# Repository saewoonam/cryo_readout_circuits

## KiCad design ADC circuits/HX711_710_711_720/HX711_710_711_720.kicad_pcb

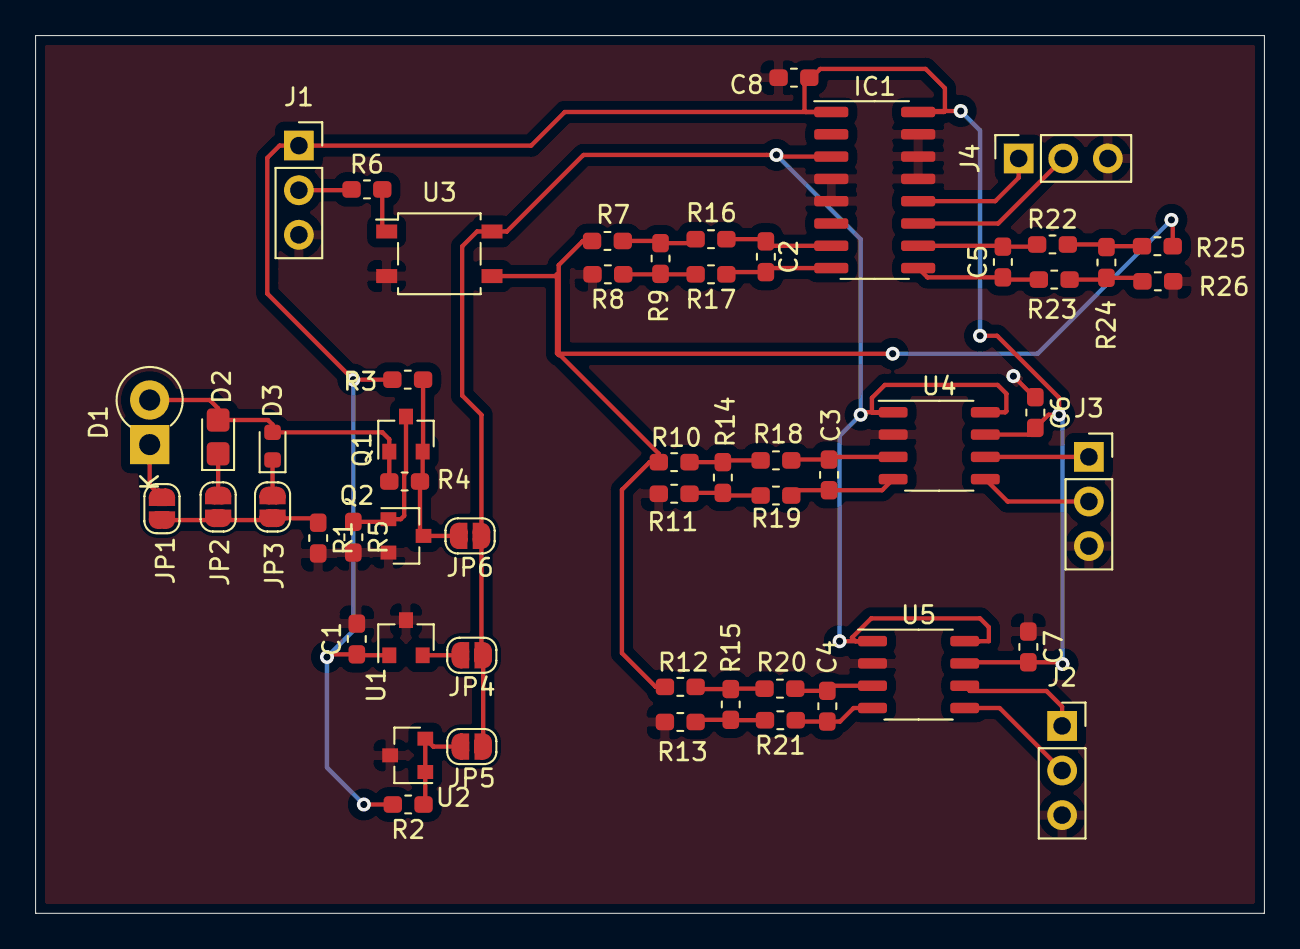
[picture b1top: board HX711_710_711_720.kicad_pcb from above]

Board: 2 copper layers, 70.0 x 50.0 mm, 55 parts (0 on the bottom side), 37 nets.

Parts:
C1: 470nF; C_0603_1608Metric_Pad1.05x0.95mm_HandSolder
C2, C3, C4, C5, C6, C7, C8: 100nF; C_0603_1608Metric_Pad1.05x0.95mm_HandSolder
D1: LTL-4231; D_DO-15_P2.54mm_Vertical_KathodeUp
D2: C2297; D_0805_2012Metric_Castellated
D3: 19-217/GHC-YR1S2/3T; D_0603_1608Metric
IC1: HX711; SOIC-16_3.9x9.9mm_P1.27mm
J1, J2, J3, J4: Conn_01x03_Female; PinSocket_1x03_P2.54mm_Vertical
JP1, JP2, JP3, JP4, JP5, JP6: NO; SolderJumper-2_P1.3mm_Open_RoundedPad1.0x1.5mm
Q1: MMBT3906; SOT-23
Q2: MMBT2222A; SOT-23
R1: 75; R_0603_1608Metric_Pad1.05x0.95mm_HandSolder
R2, R3: 300; R_0603_1608Metric_Pad1.05x0.95mm_HandSolder
R4, R5, R6, R9, R14, R15, R24: 1K; R_0603_1608Metric_Pad1.05x0.95mm_HandSolder
R7, R8, R10, R11, R12, R13, R25, R26: 10Meg; R_0603_1608Metric_Pad1.05x0.95mm_HandSolder
R16, R17, R18, R19, R20, R21, R22, R23: 100; R_0603_1608Metric_Pad1.05x0.95mm_HandSolder
U1: REF3020; SOT-23
U2: TL431DBZ; SOT-23
U3: AQW282SX; SO-4_4.4x4.3mm_P2.54mm
U4: HX710B; SOP-8_3.9x4.9mm_P1.27mm
U5: HX710C; SOP-8_3.9x4.9mm_P1.27mm

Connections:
+3V3: C1.1, C6.2, C7.2, C8.1, IC1.1, IC1.16, J1.1, R2.2, R3.2, U1.1, U4.7, U5.7
/sig: R7.2, R10.2, R12.2, R25.2, U3.3
/vref: IC1.3, JP4.1, JP5.1, JP6.1, U3.4, U4.1, U4.8, U5.1, U5.8
GND: C1.2, C6.1, C7.1, C8.2, IC1.4, IC1.5, IC1.13, IC1.14, IC1.15, J1.3, J2.3, J3.3, J4.3, Q2.2, R1.2, R5.2, R8.2, R11.2, R13.2, R26.2, U1.3, U2.3, U3.2, U4.2, U5.2
unnamed: C2.1, IC1.8, R17.1
unnamed: C2.2, IC1.7, R16.1
unnamed: C3.1, R19.1, U4.4
unnamed: C3.2, R18.1, U4.3
unnamed: C4.1, R21.1, U5.4
unnamed: C4.2, R20.1, U5.3
unnamed: C5.1, IC1.9, R23.1
unnamed: C5.2, IC1.10, R22.1
unnamed: D1.1, JP1.1
unnamed: D1.2, D2.2, D3.2, Q1.1, R4.2
unnamed: D2.1, JP2.1
unnamed: D3.1, JP3.1
unnamed: IC1.11, J4.2
unnamed: IC1.12, J4.1
unnamed: J1.2, R6.1
unnamed: J2.1, U5.6
unnamed: J2.2, U5.5
unnamed: J3.1, U4.6
unnamed: J3.2, U4.5
unnamed: JP1.2, JP2.2, JP3.2, R1.1
unnamed: JP4.2, U1.2
unnamed: JP5.2, R2.1, U2.1, U2.2
unnamed: JP6.2, Q1.2, Q2.3, R3.1, R4.1
unnamed: Q1.3, Q2.1, R5.1
unnamed: R6.2, U3.1
unnamed: R10.1, R14.1, R18.2
unnamed: R11.1, R14.2, R19.2
unnamed: R12.1, R15.1, R20.2
unnamed: R13.1, R15.2, R21.2
unnamed: R7.1, R9.1, R16.2
unnamed: R8.1, R9.2, R17.2
unnamed: R22.2, R24.1, R25.1
unnamed: R23.2, R24.2, R26.1

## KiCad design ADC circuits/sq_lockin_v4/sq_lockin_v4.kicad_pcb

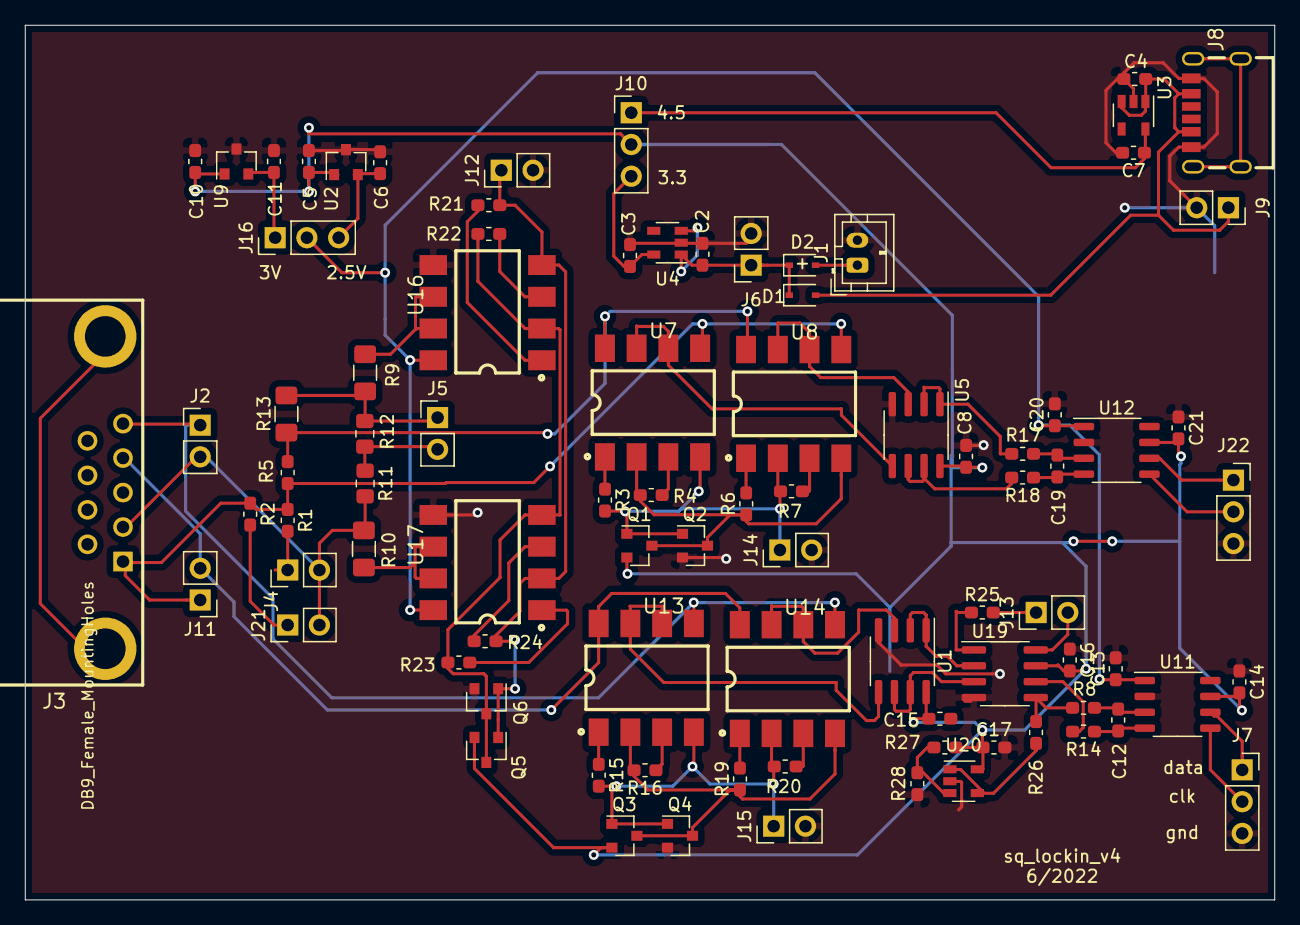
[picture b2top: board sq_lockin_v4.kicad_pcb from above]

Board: 2 copper layers, 100.0 x 70.0 mm, 88 parts (0 on the bottom side), 62 nets.

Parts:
C2, C3, C4, C5, C6, C7, C10, C11: 1uF; C_0603_1608Metric_Pad1.05x0.95mm_HandSolder
C8, C12, C13, C14, C15, C16, C17, C19, C20, C21: 100nF; C_0603_1608Metric_Pad1.05x0.95mm_HandSolder
D1, D2: LBAT54HT1G; D_SOD-323
J1: battery; JST_PH_B2B-PH-K_1x02_P2.00mm_Vertical
J2, J4, J5, J11, J12, J13, J14, J15, J21: Conn_01x02_Male_2.54mm; PinHeader_1x02_P2.54mm_Vertical
J3: DB9_Female_MountingHoles; DSUB-TH_DS1037-09FNAKT74-0CC
J6, J9: receptacle; PinSocket_1x02_P2.54mm_Vertical
J7, J22: Conn_01x03_Female; PinSocket_1x03_P2.54mm_Vertical
J8: USB_C_KoreanHroparts_6P; USB-C-KoreanHroparts
J10, J16: Conn_01x03_Male; PinHeader_1x03_P2.54mm_Vertical
Q1, Q3, Q5: BSS84; SOT-23
Q2, Q4, Q6: 2N7002; SOT-23
R1: 10K 0.1%; R_0603_1608Metric_Pad1.05x0.95mm_HandSolder
R2: 1K 0.1%; R_0603_1608Metric_Pad1.05x0.95mm_HandSolder
R3, R4, R6, R7, R15, R16, R19, R20, R21, R22, R23, R24: 200; R_0603_1608Metric_Pad1.05x0.95mm_HandSolder
R5: 100K_0.1%; R_0603_1608Metric_Pad1.05x0.95mm_HandSolder
R8, R14, R17, R18, R25: 100; R_0603_1608Metric_Pad1.05x0.95mm_HandSolder
R9, R10, R13: 1M_0.1%; R_1206_3216Metric_Pad1.42x1.75mm_HandSolder
R11: 5K_0.1%; R_0805_2012Metric_Pad1.15x1.40mm_HandSolder
R12: 75K_0.1%; R_0805_2012Metric_Pad1.15x1.40mm_HandSolder
R26: 10; R_0603_1608Metric_Pad1.05x0.95mm_HandSolder
R27, R28: 10K; R_0603_1608Metric_Pad1.05x0.95mm_HandSolder
U1, U5: OPA2376xxDGK; SOIC-8_3.9x4.9mm_P1.27mm
U2: REF3325; SOT-23
U3: LP5907MFX-4.5; SOT-23-5
U4: LP5907MFX-3.3; SOT-23-5
U7, U8, U13, U14, U16, U17: AQW212EHAX; SMD-8_L9.8-W6.4-P2.54-LS10.0-BL
U9: REF3030; SOT-23
U11, U12: HX710C; SOP-8_3.9x4.9mm_P1.27mm
U19: AD623; SOIC-8_3.9x4.9mm_P1.27mm
U20: OPA333xxDBV; SOT-23-5

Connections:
+3V3: C3.1, J10.3, U4.5
+4V: C7.1, J10.1, U3.5
/I+: J3.1, J11.1, R1.1, R2.1, R5.1, U7.5, U8.5
/I-: J2.2, J3.2, J4.2, J21.2, R10.2, R11.2
/Sheet621A3D16/in+: U5.5, U7.6, U7.7
/Sheet621A3D16/in-: U5.3, U8.6, U8.7
/Sheet624B5D4E/ctrl+: J14.1, Q1.1, Q2.1, R3.2, R7.1, U7.4, U8.2
/Sheet624B5D4E/ctrl-: Q1.3, Q2.3, R4.2, R6.1, U7.2, U8.4
/Sheet624B5D4E/in+: R5.2, R13.1, U7.8, U8.8
/Sheet6275CBF8/in+: U1.5, U13.6, U13.7
/Sheet6275CBF8/in-: U1.3, U14.6, U14.7
/Sheet62237673/V+: R18.2, U5.6, U5.7
/Sheet62237673/V-: R17.2, U5.1, U5.2
/V+: J3.4, J11.2, U13.8, U14.8
/V-: J2.1, J3.5, U13.5, U14.5
/sheet624D2E57/V+: R14.2, U19.6
/sheet624D2E57/V-: R8.2, R26.2, U19.5
/sheet624D2E58/ctrl+: J15.1, Q3.1, Q4.1, R15.2, R20.1, U13.4, U14.2
/sheet624D2E58/ctrl-: Q3.3, Q4.3, R16.2, R19.1, U13.2, U14.4
/sheet6256EE2A/ctrl+: J12.1, Q5.1, Q6.1, R21.2, R24.1, U16.4, U17.2
/sheet6256EE2A/ctrl-: Q5.3, Q6.3, R22.2, R23.1, U16.2, U17.4
/sheet6256EE2A/out+: R9.2, U16.6, U16.7
/sheet6256EE2A/out-: R10.1, U17.6, U17.7
/vref: C13.1, C20.1, J16.2, U11.1, U12.1, U16.8, U17.8
/vref1: C6.1, J16.3, U2.2
/vref2: C11.1, J16.1, U9.2
GND: C2.2, C3.2, C4.2, C5.2, C6.2, C7.2, C8.2, C10.2, C11.2, C13.2, C14.1, C16.1, C17.2, C20.2, C21.1, J1.2, J6.2, J7.3, J8.A12, J8.B12, J9.2, J12.2, J14.2, J15.2, J22.3, Q2.2, Q4.2, Q6.2, R28.2, U1.4, U2.3, U3.2, U4.2, U5.4, U9.3, U11.2, U12.2, U16.5, U17.5, U19.4, U20.2
unnamed: C2.1, D1.1, D2.1, J6.1, U4.1, U4.3
unnamed: C4.1, D1.2, J8.A9, J8.B9, J9.1, U3.1, U3.3
unnamed: C12.1, R14.1, U11.4
unnamed: C12.2, R8.1, U11.3
unnamed: C19.1, R18.1, U12.4
unnamed: C19.2, R17.1, U12.3
unnamed: D2.2, J1.1
unnamed: J4.1, R1.2
unnamed: J5.1, R9.1, R12.1, R13.2
unnamed: J5.2, R11.1, R12.2
unnamed: J7.1, U11.6
unnamed: J7.2, U11.5
unnamed: J13.1, R25.2
unnamed: J13.2, U19.8
unnamed: J21.1, R2.2
unnamed: J22.1, U12.6
unnamed: J22.2, U12.5
unnamed: R3.1, U7.1
unnamed: R4.1, U7.3
unnamed: R6.2, U8.1
unnamed: R7.2, U8.3
unnamed: R15.1, U13.1
unnamed: R16.1, U13.3
unnamed: R19.2, U14.1
unnamed: R20.2, U14.3
unnamed: R21.1, U16.1
unnamed: R22.1, U16.3
unnamed: R23.2, U17.1
unnamed: R24.2, U17.3
unnamed: R25.1, U19.1
unnamed: R26.1, U20.1, U20.4
unnamed: R27.2, R28.1, U20.3
unnamed: U1.1, U1.2, U19.2
unnamed: U1.6, U1.7, U19.3
VCC: C5.1, C8.1, C10.1, C14.2, C15.1, C16.2, C17.1, C21.2, J10.2, Q1.2, Q3.2, Q5.2, R27.1, U1.8, U2.1, U5.8, U9.1, U11.7, U12.7, U19.7, U20.5

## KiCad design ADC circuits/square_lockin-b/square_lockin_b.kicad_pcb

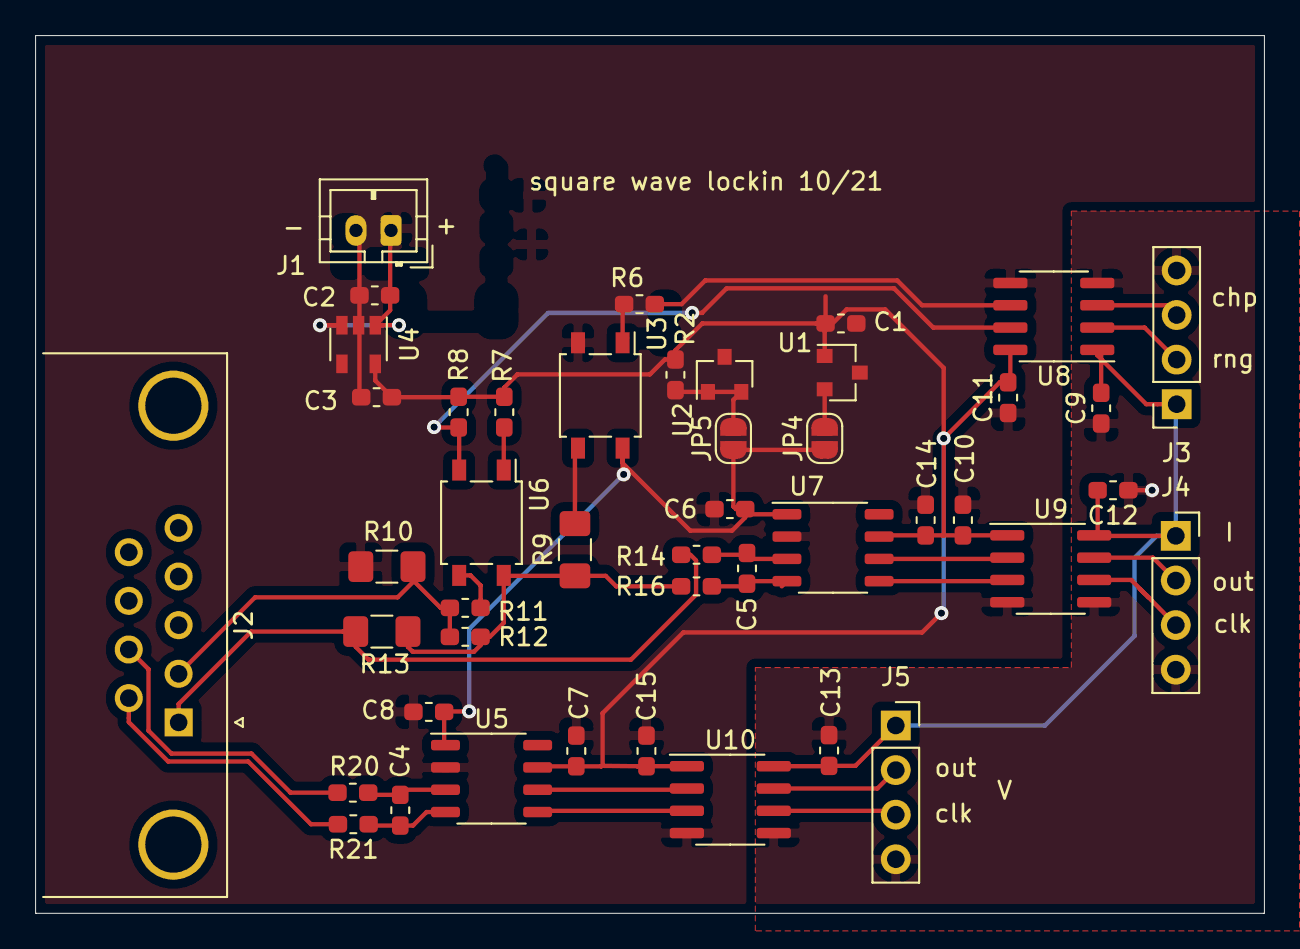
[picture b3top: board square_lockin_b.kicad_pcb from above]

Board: 2 copper layers, 70.0 x 50.0 mm, 45 parts (0 on the bottom side), 33 nets.

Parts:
C1: 470nF; C_0603_1608Metric_Pad1.05x0.95mm_HandSolder
C2, C3: 1uF; C_0603_1608Metric_Pad1.05x0.95mm_HandSolder
C4, C5, C6, C7, C8, C9, C10, C11, C12, C13, C14, C15: 100nF; C_0603_1608Metric_Pad1.05x0.95mm_HandSolder
J1: JST-B2B-PH; JST_PH_B2B-PH-K_1x02_P2.00mm_Vertical
J2: DB9_Female; DSUB-9_Female_Horizontal_P2.77x2.84mm_EdgePinOffset4.94mm_H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
J3, J4, J5: Conn_01x04_Female; PinSocket_1x04_P2.54mm_Vertical
JP4, JP5: NO; SolderJumper-2_P1.3mm_Open_RoundedPad1.0x1.5mm
R2: 300; R_0603_1608Metric_Pad1.05x0.95mm_HandSolder
R6, R7, R8: 1K; R_0603_1608Metric_Pad1.05x0.95mm_HandSolder
R9, R10, R13: 1M_0.1%; R_1206_3216Metric_Pad1.42x1.75mm_HandSolder
R11: 2.2K_0.1%; R_0603_1608Metric_Pad1.05x0.95mm_HandSolder
R12: 22K_0.1%; R_0603_1608Metric_Pad1.05x0.95mm_HandSolder
R14, R16, R20, R21: 100; R_0603_1608Metric_Pad1.05x0.95mm_HandSolder
U1: REF3020; SOT-23
U2: TL431DBZ; SOT-23
U3, U6: AQW282SX; SO-4_4.4x4.3mm_P2.54mm
U4: LP5907MFX-3.3; SOT-23-5
U5, U7: HX710C; SOP-8_3.9x4.9mm_P1.27mm
U8: PI120; SOIC-8_3.9x4.9mm_P1.27mm
U9, U10: PI121; SOIC-8_3.9x4.9mm_P1.27mm

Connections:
+3.3VP: C9.2, C12.2, C13.2, J3.1, J4.1, J5.1, U8.1, U9.8, U10.8
+3V3: C1.1, C3.1, C7.2, C10.2, C11.2, C14.2, C15.2, R2.2, R7.2, R8.2, U1.1, U4.5, U5.7, U7.7, U8.8, U9.1, U10.1
/I+: J2.1, R13.1, R14.2
/I-: J2.2, R10.1, R11.2, R12.2
/V+: J2.6, R21.2
/V-: J2.7, R20.2
/range_toggle: R8.1, U6.2, U8.7
/sig: R9.2, U3.3
/vref: C6.1, C8.1, JP4.1, JP5.1, U3.4, U5.1, U7.1
GND: C1.2, C2.2, C3.2, C6.2, C7.1, C8.2, C10.1, C11.1, C14.1, C15.1, J1.2, R10.2, U1.3, U2.3, U3.2, U4.2, U5.2, U7.2, U8.5, U9.4, U10.4
GNDD: C9.1, C12.1, C13.1, J3.4, J4.4, J5.4, U8.4, U9.5, U10.5
unnamed: C2.1, J1.1, U4.1, U4.3
unnamed: C4.1, R21.1, U5.4
unnamed: C4.2, R20.1, U5.3
unnamed: C5.1, R16.1, U7.4
unnamed: C5.2, R14.1, U7.3
unnamed: J3.2, U8.2
unnamed: J3.3, U8.3
unnamed: J4.2, U9.7
unnamed: J4.3, U9.6
unnamed: J5.2, U10.7
unnamed: J5.3, U10.6
unnamed: JP4.2, U1.2
unnamed: JP5.2, R2.1, U2.1, U2.2
unnamed: R6.1, U8.6
unnamed: R6.2, U3.1
unnamed: R7.1, U6.1
unnamed: R11.1, U6.3
unnamed: R9.1, R12.1, R13.2, R16.2, U6.4
unnamed: U7.5, U9.3
unnamed: U7.6, U9.2
unnamed: U5.6, U10.2
unnamed: U5.5, U10.3

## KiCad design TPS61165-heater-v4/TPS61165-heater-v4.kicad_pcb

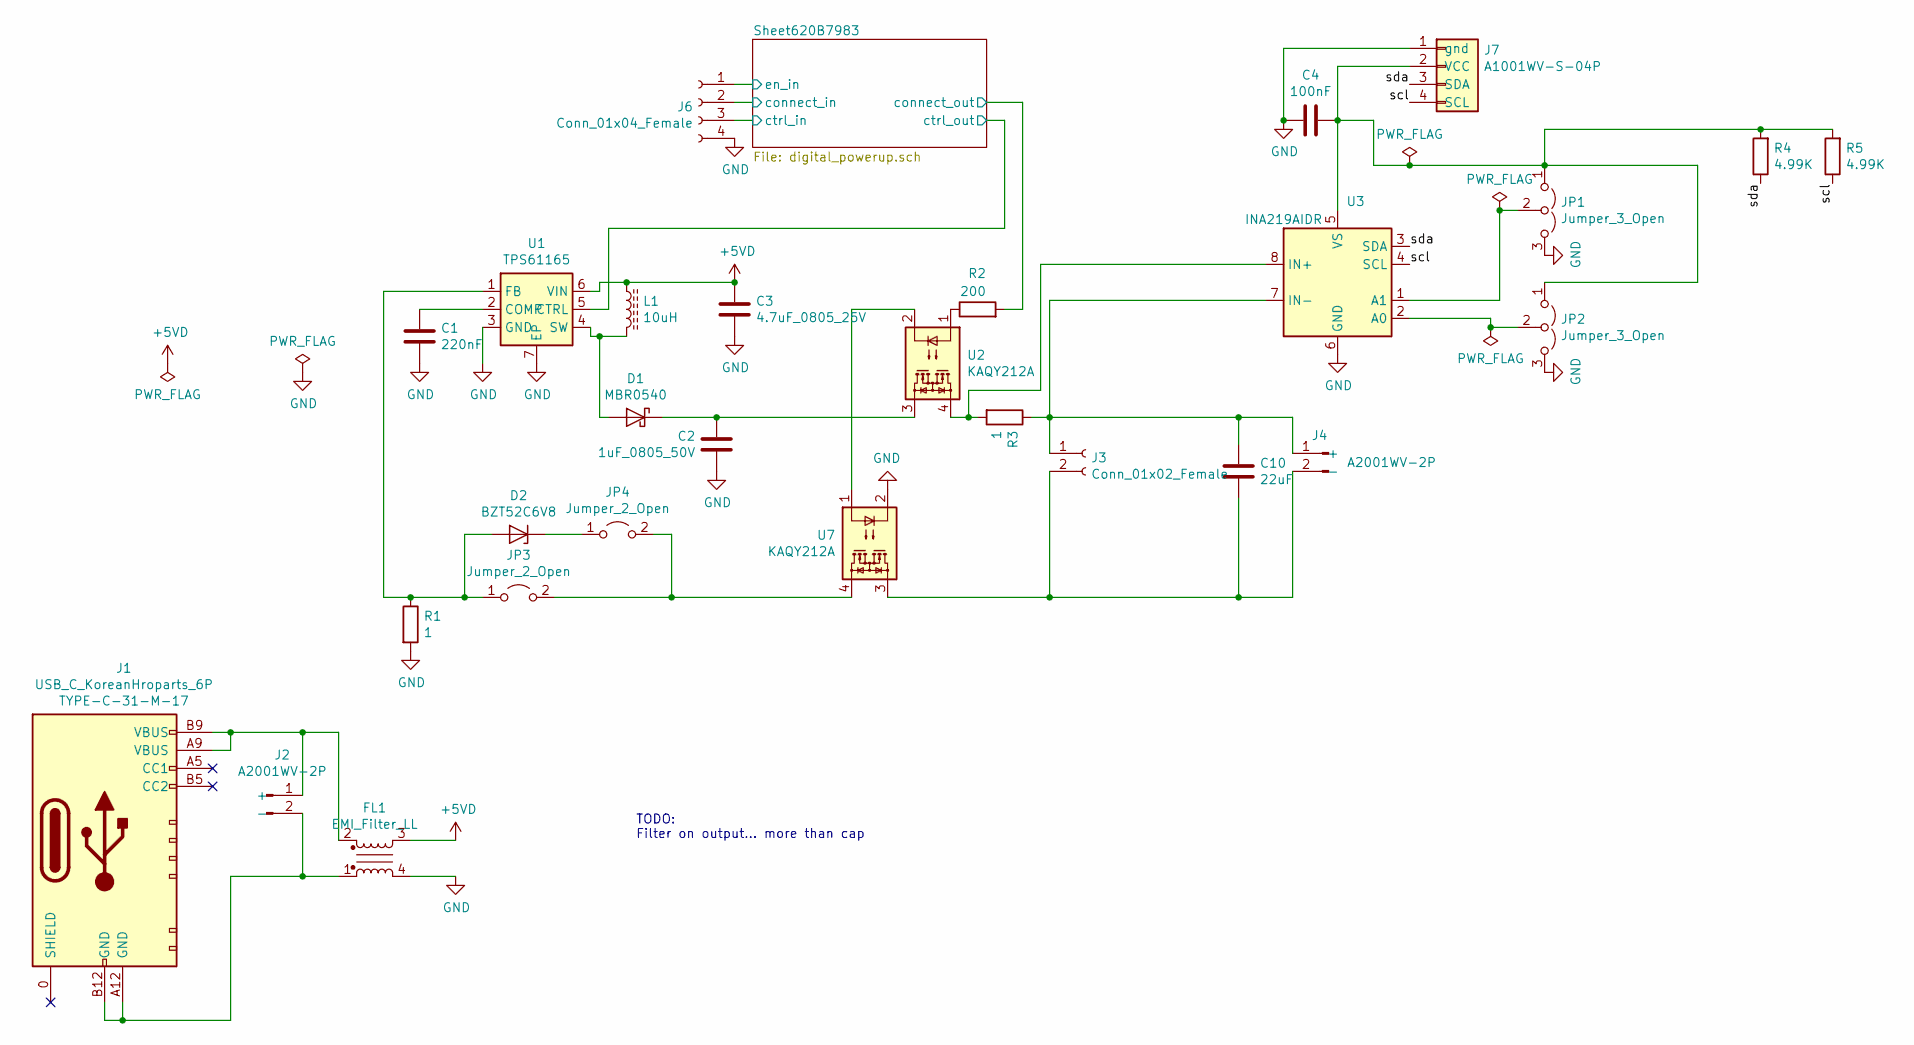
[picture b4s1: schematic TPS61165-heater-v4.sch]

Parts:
C1: 220nF; C_0603_1608Metric_Pad1.05x0.95mm_HandSolder; MPN CL10B224KA8NNNC; LCSC C21120
C2: 1uF_0805_50V; C_0805_2012Metric_Pad1.15x1.40mm_HandSolder; MPN CL21B105KBFNNNE; LCSC C28323
C3: 4.7uF_0805_25V; C_0805_2012Metric_Pad1.15x1.40mm_HandSolder; MPN CC0805KKX7R8BB475; LCSC C354262
C4: 100nF; C_0603_1608Metric_Pad1.05x0.95mm_HandSolder; MPN CC0603KRX7R9BB104; LCSC C14663
C10: 22uF; C_2220_5650Metric_Pad1.97x5.40mm_HandSolder; MPN FS55X226K500EHG; LCSC C784103
D1: MBR0540; D_SOD-123; MPN MBR0540T1G; LCSC C21353
D2: BZT52C6V8; D_SOD-123; MPN BZT52C6V8; LCSC C173404
FL1: EMI_Filter_LL; FILTER-SMD_4P-L4.5-W3.2-BL_CMF4532L_1812; MPN ACT45L-201-2P-TL000; LCSC C131445
J1: USB_C_KoreanHroparts_6P; USB-C-KoreanHroparts; MPN TYPE-C-31-M-17; LCSC C283540
J2, J4: A2001WV-2P; JST_PH_B2B-PH-K_1x02_P2.00mm_Vertical; MPN A2001WV-2P; LCSC C225188
J3: Conn_01x02_Female; PinSocket_1x02_P2.54mm_Vertical; LCSC C49661
J6: Conn_01x04_Female; PinSocket_1x04_P2.54mm_Vertical; MPN B-2200S04P-A120; LCSC C124413
J7: A1001WV-S-04P; JST_SH_BM04B-SRSS-TB_1x04-1MP_P1.00mm_Vertical; MPN A1001WV-S-04P; LCSC C371588
JP1, JP2: Jumper_3_Open; SolderJumper-3_P1.3mm_Open_Pad1.0x1.5mm
JP3, JP4: Jumper_2_Open; SolderJumper-2_P1.3mm_Open_RoundedPad1.0x1.5mm
L1: 10uH; IND-SMD_L4.7-W4.7; MPN VLCF5020T-100M1R1-1; LCSC C212280
R1, R3: 1; R_0603_1608Metric_Pad1.05x0.95mm_HandSolder; MPN 0603WAF100KT5E; LCSC C22936
R2: 200; R_0603_1608Metric_Pad1.05x0.95mm_HandSolder; MPN 0603WAF2000T5E; LCSC C8218
R4, R5: 4.99K; R_0603_1608Metric_Pad1.05x0.95mm_HandSolder; MPN 0603WAF4991T5E; LCSC C23046
U1: TPS61165; WSON-6-1EP_2x2mm_P0.65mm_EP1x1.6mm; MPN TPS61165DRVR; LCSC C122568
U2, U7: KAQY212A; SMD-4_L4.6-W6.4-P2.54-LS10.0-BR; MPN KAQY212A; LCSC C194713
U3: INA219AIDR; SOIC-8_3.9x4.9mm_P1.27mm; MPN INA219AIDR; LCSC C138706

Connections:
+5VD: C3.1, FL1.3, L1.1, U1.6 (VIN); also elsewhere on the board
/Sheet620B7983/connect_in: J6.2; also elsewhere on the board
/Sheet620B7983/connect_out: R2.2; also elsewhere on the board
/Sheet620B7983/ctrl_in: J6.3; also elsewhere on the board
/Sheet620B7983/ctrl_out: U1.5 (CTRL); also elsewhere on the board
/Sheet620B7983/en_in: J6.1; also elsewhere on the board
/scl: J7.4 (SCL), R5.1, U3.4 (SCL)
/sda: J7.3 (SDA), R4.1, U3.3 (SDA)
GND: C1.2, C2.2, C3.2, C4.2, FL1.4, J6.4, J7.1 (gnd), JP1.3 (B), JP2.3 (B), R1.2, U1.3 (GND), U1.7 (EP), U3.6 (GND), U7.2; also elsewhere on the board
unnamed: C1.1, U1.2 (COMP)
unnamed: C2.1, D1.1 (K), U2.3
unnamed: C4.1, J7.2 (VCC), JP1.1 (A), JP2.1 (A), R4.2, R5.2, U3.5 (VS)
unnamed: C10.1, J3.1, J4.1 (+), R3.1, U3.7 (IN-)
unnamed: C10.2, J3.2, J4.2 (-), U7.3
unnamed: D1.2 (A), L1.2, U1.4 (SW)
unnamed: D2.1 (K), JP4.1 (A)
unnamed: D2.2 (A), JP3.1 (A), R1.1, U1.1 (FB)
unnamed: FL1.1, J1.A12 (GND), J1.B12 (GND), J2.2 (-)
unnamed: FL1.2, J1.A9 (VBUS), J1.B9 (VBUS), J2.1 (+)
unnamed: JP1.2 (C), U3.1 (A1)
unnamed: JP2.2 (C), U3.2 (A0)
unnamed: JP3.2 (B), JP4.2 (B), U7.4
unnamed: R2.1, U2.1
unnamed: R3.2, U2.4, U3.8 (IN+)
unnamed: U2.2, U7.1

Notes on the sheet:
TODO: Filter on output… more than cap

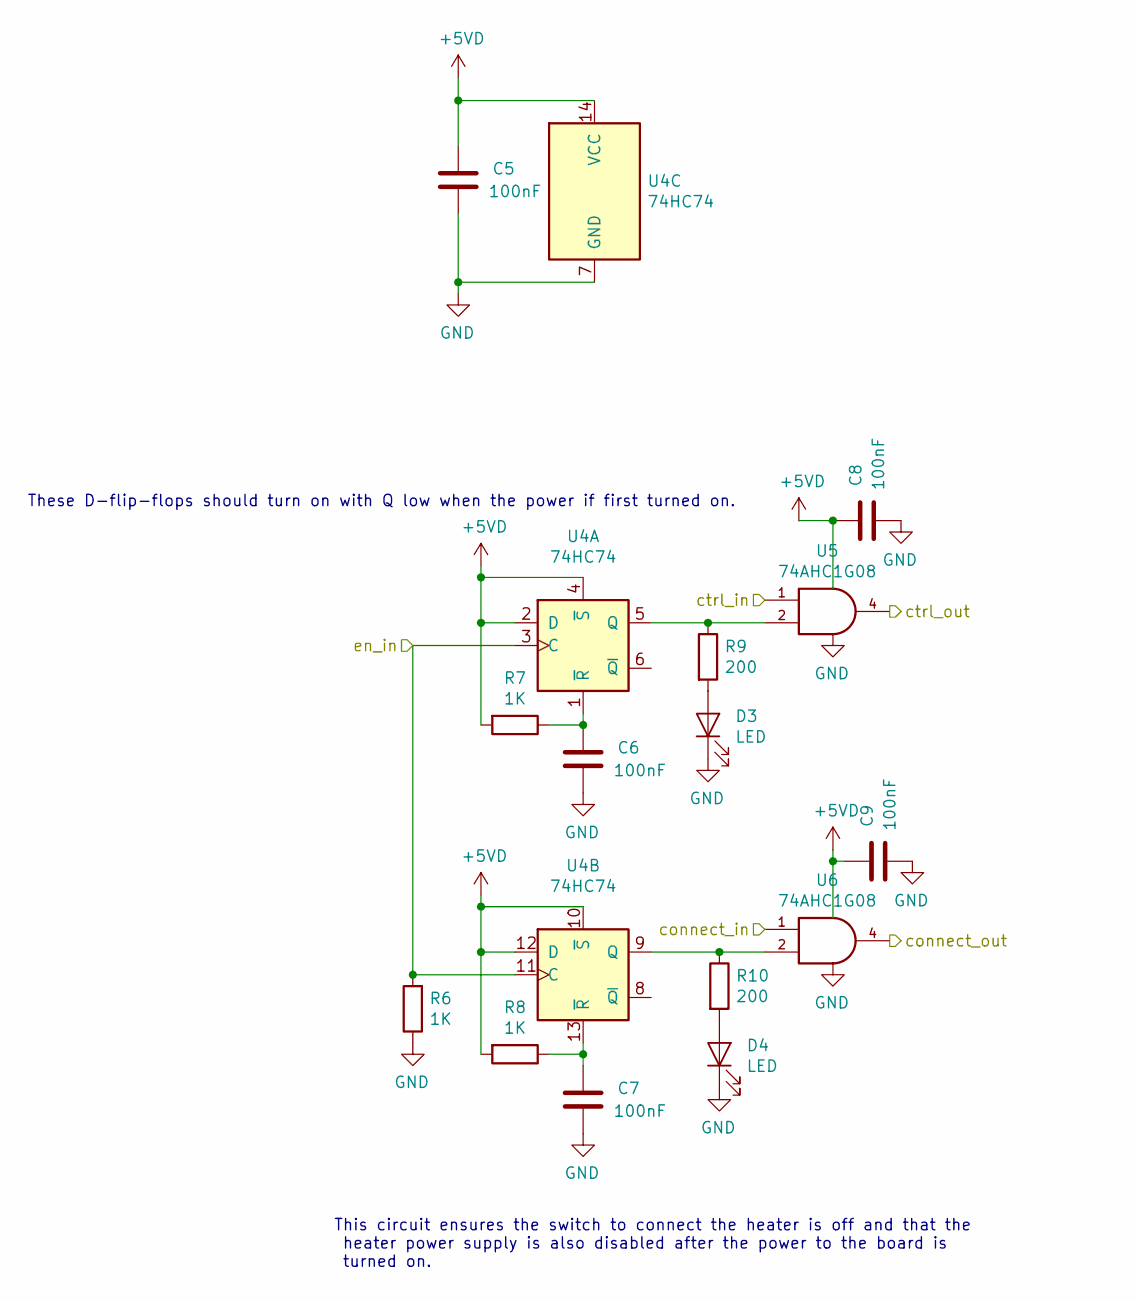
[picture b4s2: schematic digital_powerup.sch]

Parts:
C5, C6, C7, C8, C9: 100nF; C_0603_1608Metric_Pad1.05x0.95mm_HandSolder; MPN CC0603KRX7R9BB104; LCSC C14663
D3, D4: LED; LED_0603_1608Metric_Pad1.05x0.95mm_HandSolder; MPN KT-0603R; LCSC C2286
R6, R7, R8: 1K; R_0603_1608Metric_Pad1.05x0.95mm_HandSolder; MPN 0603WAF1001T5E; LCSC C21190
R9, R10: 200; R_0603_1608Metric_Pad1.05x0.95mm_HandSolder; MPN 0603WAF2000T5E; LCSC C8218
U4: 74HC74; SOIC-14_3.9x8.7mm_P1.27mm; MPN 74HC74D,653; LCSC C27597
U5, U6: 74AHC1G08; SOT-23-5_HandSoldering; MPN MC74HC1G08DTT1G; LCSC C108694

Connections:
+5VD: C5.1, C8.1, C9.1, R7.2, R8.2, U4.2 (D), U4.4 (~S), U4.10 (~S), U4.12 (D), U4.14 (VCC), U5.5 (VCC), U6.5 (VCC); also elsewhere on the board
/Sheet620B7983/connect_in: U6.1; also elsewhere on the board
/Sheet620B7983/connect_out: U6.4; also elsewhere on the board
/Sheet620B7983/ctrl_in: U5.1; also elsewhere on the board
/Sheet620B7983/ctrl_out: U5.4; also elsewhere on the board
/Sheet620B7983/en_in: R6.2, U4.3 (C), U4.11 (C); also elsewhere on the board
GND: C5.2, C6.2, C7.2, C8.2, C9.2, D3.1 (K), D4.1 (K), R6.1, U4.7 (GND), U5.3 (GND), U6.3 (GND); also elsewhere on the board
unnamed: C6.1, R7.1, U4.1 (~R)
unnamed: C7.1, R8.1, U4.13 (~R)
unnamed: D3.2 (A), R9.2
unnamed: D4.2 (A), R10.2
unnamed: R9.1, U4.5 (Q), U5.2
unnamed: R10.1, U4.9 (Q), U6.2

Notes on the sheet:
This circuit ensures the switch to connect the heater is off and that the heater power supply is also disabled after the power to the board is turned on.
These D-flip-flops should turn on with Q low when the power if first turned on.

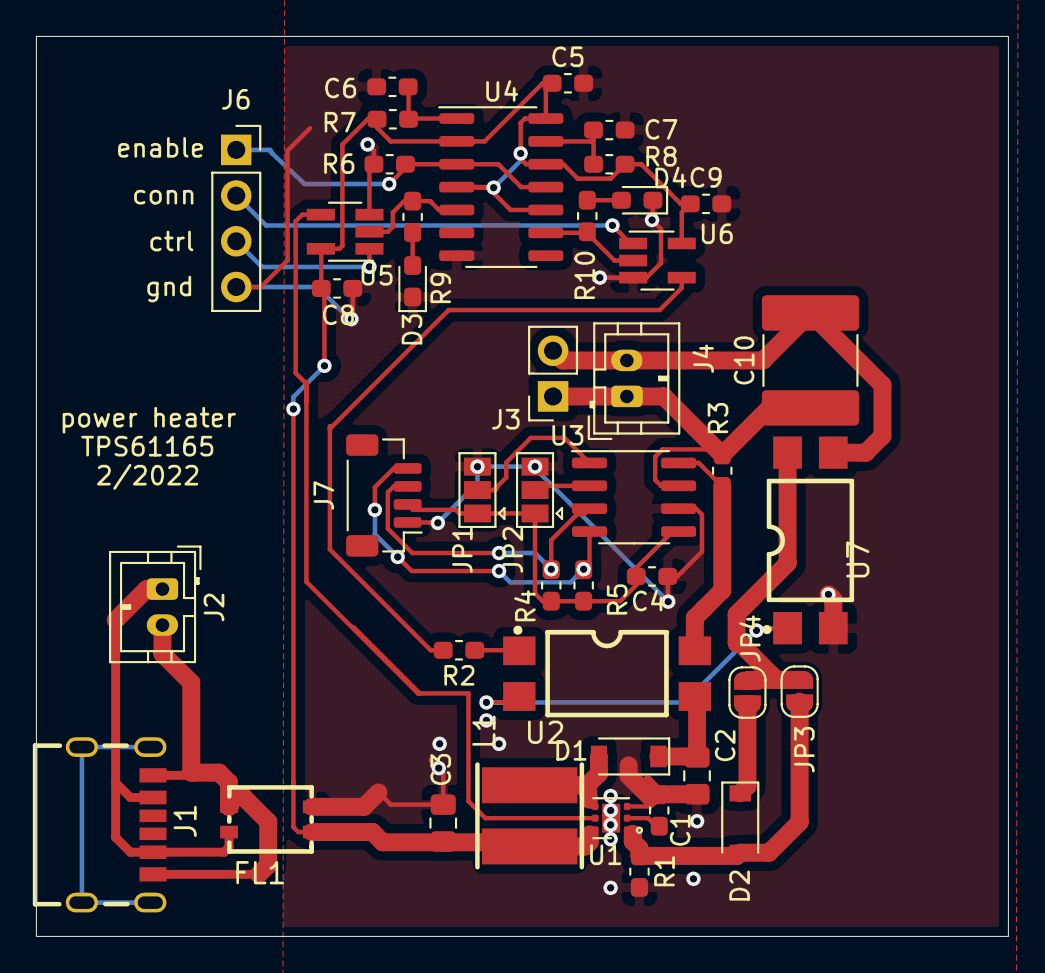
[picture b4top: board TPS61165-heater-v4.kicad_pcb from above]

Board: 2 copper layers, 54.0 x 50.0 mm, 43 parts (0 on the bottom side), 31 nets.

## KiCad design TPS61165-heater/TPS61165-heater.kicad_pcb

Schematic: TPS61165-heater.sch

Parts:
C1: 220nF; C_0603_1608Metric_Pad1.05x0.95mm_HandSolder; MPN CL10B224KA8NNNC; LCSC C21120
C2: 1uF_0805_50V; C_0805_2012Metric_Pad1.15x1.40mm_HandSolder; MPN CL21B105KBFNNNE; LCSC C28323
C3: 4.7uF_0805_25V; C_0805_2012Metric_Pad1.15x1.40mm_HandSolder; MPN CC0805KKX7R8BB475; LCSC C354262
C4: 100nF; C_0603_1608Metric_Pad1.05x0.95mm_HandSolder; MPN CC0603KRX7R9BB104; LCSC C14663
D1: MBR0540; D_SOD-123; MPN MBR0540T1G; LCSC C21353
FL1: EMI_Filter_LL; LL_FILTER-SMD_4P-L9.2-W6.0-TL; MPN CYSCM0905RTL-501; LCSC C261397
J1: USB_C_KoreanHroparts_6P; USB-C-KoreanHroparts; MPN TYPE-C-31-M-17; LCSC C283540
J2, J4: A2001WV-2P; JST_PH_B2B-PH-K_1x02_P2.00mm_Vertical; MPN A2001WV-2P; LCSC C225188
J3: Conn_01x02_Female; PinSocket_1x02_P2.54mm_Vertical; LCSC C49661
J5: MMCX; MMCX_JLC; MPN KH-MMCX-Z; LCSC C530664
J6: Conn_01x03_Female; PinSocket_1x03_P2.54mm_Vertical; LCSC C146243
J7: A1001WV-S-04P; JST_SH_BM04B-SRSS-TB_1x04-1MP_P1.00mm_Vertical; MPN A1001WV-S-04P; LCSC C371588
JP1, JP2: Jumper_3_Open; SolderJumper-3_P1.3mm_Open_Pad1.0x1.5mm
L1: 10uH; IND-SMD_L4.7-W4.7; MPN VLCF5020T-100M1R1-1; LCSC C89448
R1, R3: 1; R_0603_1608Metric_Pad1.05x0.95mm_HandSolder; MPN 0603WAF100KT5E; LCSC C22936
R2: 390; R_0603_1608Metric_Pad1.05x0.95mm_HandSolder; MPN 0603WAF3900T5E; LCSC C23151
R4, R5: 4.99K; R_0603_1608Metric_Pad1.05x0.95mm_HandSolder; MPN 0603WAF4991T5E; LCSC C23046
U1: TPS61165; WSON-6-1EP_2x2mm_P0.65mm_EP1x1.6mm; MPN TPS61165DRVR; LCSC C122568
U2: KAQY212A; SMD-4_L4.6-W6.4-P2.54-LS10.0-BR; MPN KAQY212A; LCSC C194713
U3: INA226; VSSOP-10_3x3mm_P0.5mm; MPN INA226AIDGSR; LCSC C49851

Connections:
+5VD: C3.1, FL1.3, L1.1, U1.6
/scl: J7.4 (SCL), R5.1, U3.5 (SCL)
/sda: J7.3 (SDA), R4.1, U3.4 (SDA)
GND: C1.2, C2.2, C3.2, C4.2, FL1.4, J5.2 (Ext), J6.3, J7.1 (gnd), JP1.3 (B), JP2.3 (B), R1.2, U1.3, U1.7, U2.2, U3.7 (GND)
unnamed: C1.1, U1.2
unnamed: C2.1, D1.1 (K), U2.3
unnamed: C4.1, J7.2 (VCC), JP1.1 (A), JP2.1 (A), R4.2, R5.2, U3.6 (VS)
unnamed: D1.2 (A), L1.2, U1.4
unnamed: FL1.1, J1.A12 (GND), J1.B12 (GND), J2.2 (-)
unnamed: FL1.2, J1.A9 (VBUS), J1.B9 (VBUS), J2.1 (+)
unnamed: J3.1, J4.1 (+), J5.1 (In), R3.1, U3.9 (Vin-)
unnamed: J3.2, J4.2 (-), R1.1, U1.1
unnamed: J6.1, U1.5
unnamed: J6.2, R2.1
unnamed: JP1.2 (C), U3.1 (A1)
unnamed: JP2.2 (C), U3.2 (A0)
unnamed: R2.2, U2.1
unnamed: R3.2, U2.4, U3.8 (Vbus), U3.10 (Vin+)

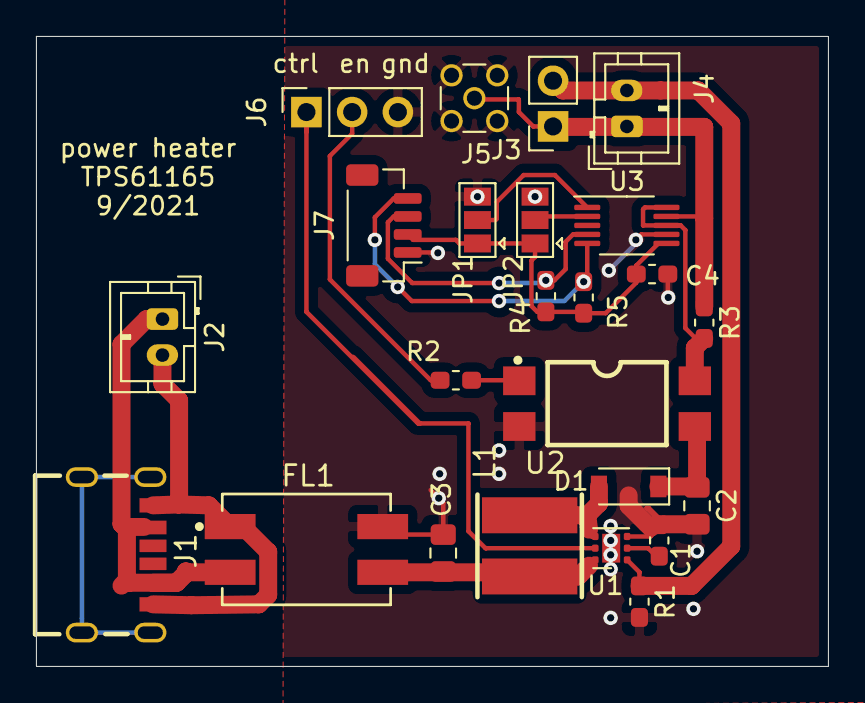
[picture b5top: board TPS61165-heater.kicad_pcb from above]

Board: 2 copper layers, 44.0 x 35.0 mm, 24 parts (0 on the bottom side), 18 nets.
